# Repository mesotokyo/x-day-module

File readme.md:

# X-DAY (a.k.a. musicboxmod)

X-DAY (development name: musicboxmod) is a music box synthesizer module using HK326 IC. Based on the reference circuit, but modified to allow playback speed (and pitch) control. In addition, this module can output a gate signal linked to the melody.

## Controls, inputs and outputs

 - `START` button: Playback ON/OFF control. The behavior depoends on jumper pin settings
 - `SPEED` knob: Control playback speed. Also pitch changes with playback speed
 - `MOD CV IN`: Modulation input to change the playback speed
 - `TRIG IN`: Trigger input to control Playback ON/OFF (the same as `START` button)
 - `AUDIO OUT`: Audio signal output
 - `GATE OUT`: Gate signal output
 - `CV OFFSET`(trimmer resistor on PCB): You can change CV input offset. Recommended position is almost "2 o'clock" 
 - `MODE` (jumper pin on PCB): You can change the  behavior of the `START` button and the `TRIG IN` input. See table 1.
 - `SL` (jumper pin on PCB): You can change the  behavior of the `START` button and the `TRIG IN` input. See table 1.

### Table 1: `MODE` and `SL` jumper pin settings

| MODE pin setting | SL pin setting | Behavior |
| ---------------- | -------------- | -------- |
| Vdd              | Vdd            | ON/OFF   |
| Vdd              | Vss            | ONE SHOT, NON RE-TRIGGER |
| Vss              | Vdd            | ONE SHOT, RE-TRIGGER |
| Vss              | Vss            | PLAY ALL SONGS |

 - note 1: `Vss` is opposite position of `Vdd`.
 - note 2: `ONE SHOT` means "play one song and then stop".
 - note 3: `RE-TRIGGER` means "stop current song and play next song when the button is pushed".

## Schematic

## PCB image

## KiCAD files

This KiCAD project uses my KiCAD footprint and symbol library (https://github.com/mesotokyo/mst-kicad-lib). If you want to modify the schematic and PCB, please import this library.

## gerber

Please check [gerber](gerber) directory.

# Licenses

Creative Commons CC-BY 4.0 (https://creativecommons.org/licenses/by/4.0/)

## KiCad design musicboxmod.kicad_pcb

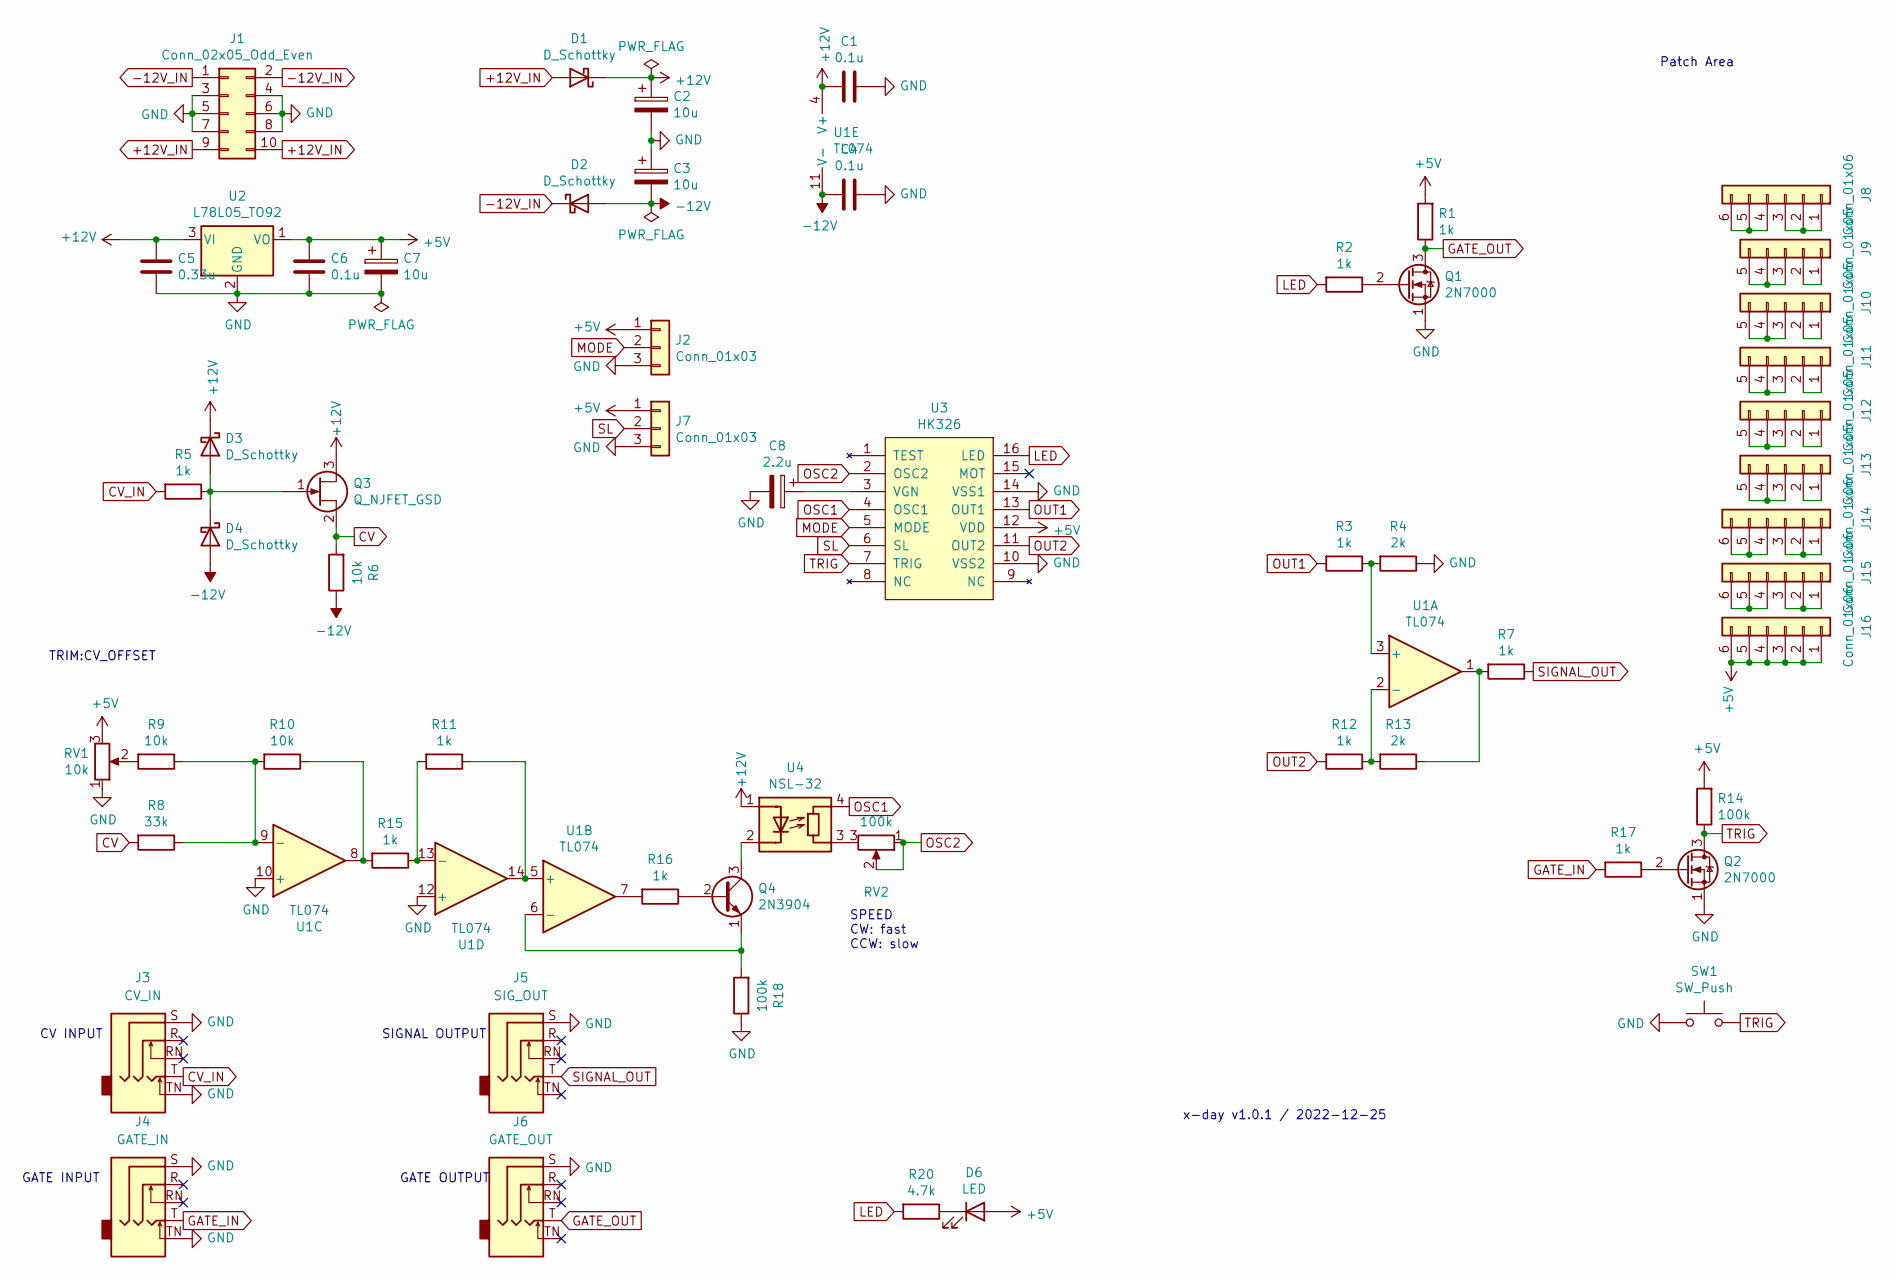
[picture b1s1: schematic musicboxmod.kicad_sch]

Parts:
C1, C4, C6: 0.1u; C_Disc_D3.0mm_W1.6mm_P2.50mm
C2, C3, C7: 10u; CP_Radial_D5.0mm_P2.50mm
C5: 0.33u; C_Disc_D3.0mm_W1.6mm_P2.50mm
C8: 2.2u; C_Disc_D3.0mm_W1.6mm_P2.50mm
D1, D2, D3, D4: D_Schottky; D_DO-34_SOD68_P7.62mm_Horizontal
D6: LED; LED_D3.0mm
J1: Conn_02x05_Odd_Even; IDC-Header_2x05_P2.54mm_Vertical
J2, J7: Conn_01x03; PinSocket_1x03_P2.54mm_Vertical
J3: CV_IN; Jack_3.5mm_CUI_SJ1-3535NG_Horizontal
J4: GATE_IN; Jack_3.5mm_CUI_SJ1-3535NG_Horizontal
J5: SIG_OUT; Jack_3.5mm_CUI_SJ1-3535NG_Horizontal
J6: GATE_OUT; Jack_3.5mm_CUI_SJ1-3535NG_Horizontal
J8, J14, J15, J16: Conn_01x06; PinHeader_1x06_P2.54mm_Vertical
J9, J10, J11, J12, J13: Conn_01x05; PinHeader_1x05_P2.54mm_Vertical
Q1, Q2: 2N7000; TO-92
Q3: Q_NJFET_GSD; TO-92
Q4: 2N3904; TO-92
R1, R2, R3, R5, R7, R11, R12, R15, R16, R17: 1k; R_Axial_DIN0204_L3.6mm_D1.6mm_P7.62mm_Horizontal
R4, R13: 2k; R_Axial_DIN0204_L3.6mm_D1.6mm_P7.62mm_Horizontal
R6, R9, R10: 10k; R_Axial_DIN0204_L3.6mm_D1.6mm_P7.62mm_Horizontal
R8: 33k; R_Axial_DIN0204_L3.6mm_D1.6mm_P7.62mm_Horizontal
R14, R18: 100k; R_Axial_DIN0204_L3.6mm_D1.6mm_P7.62mm_Horizontal
R20: 4.7k; R_Axial_DIN0204_L3.6mm_D1.6mm_P7.62mm_Horizontal
RV1: 10k; Potentiometer_Bourns_3339S_Horizontal
RV2: 100k; Potentiometer_Alps_RK097_Single_Horizontal
SW1: SW_Push; PinHeader_1x02_P2.54mm_Vertical
U1: TL074; DIP-14_W7.62mm_Socket
U2: L78L05_TO92; TO-92
U3: HK326; DIP-16_W7.62mm_Socket
U4: NSL-32; Luna_NSL-32

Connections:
+5V: C6.2, C7.1, D6.2 (A), J2.1, J7.1, J16.1, J16.2, J16.3, J16.4, J16.5, J16.6, R1.2, R14.2, RV1.3, U2.1 (VO), U3.12 (VDD)
+12V: C1.1, C2.1, C5.2, D1.1 (K), D3.1 (K), Q3.3 (D), U1.4 (V+), U2.3 (VI), U4.1 (A)
+12V_IN: D1.2 (A), J1.9, J1.10
-12V: C3.2, C4.1, D2.2 (A), D4.2 (A), R6.1, U1.11 (V-)
-12V_IN: D2.1 (K), J1.1, J1.2
CV: Q3.2 (S), R6.2, R8.2
CV_IN: J3.T, R5.2
GATE_IN: J4.T, R17.2
GATE_OUT: J6.T, Q1.3 (D), R1.1
GND: C1.2, C2.2, C3.1, C4.2, C5.1, C6.1, C7.2, C8.2, J1.3, J1.4, J1.5, J1.6, J1.7, J1.8, J2.3, J3.S, J3.TN, J4.S, J4.TN, J5.S, J6.S, J7.3, Q1.1 (S), Q2.1 (S), R4.1, R18.1, RV1.1, SW1.1, U1.10 (+), U1.12 (+), U2.2 (GND), U3.10 (VSS2), U3.14 (VSS1)
LED: R2.2, R20.2, U3.16 (LED)
MODE: J2.2, U3.5 (MODE)
unnamed: C8.1, U3.3 (VGN)
unnamed: D3.2 (A), D4.1 (K), Q3.1 (G), R5.1
unnamed: D6.1 (K), R20.1
unnamed: J8.1, J8.2, J8.3
unnamed: J8.4, J8.5, J8.6
unnamed: J9.1, J9.2
unnamed: J9.3, J9.4, J9.5
unnamed: J10.1, J10.2
unnamed: J10.3, J10.4, J10.5
unnamed: J11.1, J11.2
unnamed: J11.3, J11.4, J11.5
unnamed: J12.1, J12.2
unnamed: J12.3, J12.4, J12.5
unnamed: J13.1, J13.2
unnamed: J13.3, J13.4, J13.5
unnamed: J14.1, J14.2, J14.3
unnamed: J14.4, J14.5, J14.6
unnamed: J15.1, J15.2, J15.3
unnamed: J15.4, J15.5, J15.6
unnamed: Q1.2 (G), R2.1
unnamed: Q2.2 (G), R17.1
unnamed: Q4.1 (E), R18.2, U1.6 (-)
unnamed: Q4.2 (B), R16.1
unnamed: Q4.3 (C), U4.2 (K)
unnamed: R3.1, R4.2, U1.3 (+)
unnamed: R9.2, RV1.2
unnamed: R10.1, R15.2, U1.8
unnamed: R8.1, R9.1, R10.2, U1.9 (-)
unnamed: R11.1, U1.5 (+), U1.14
unnamed: R11.2, R15.1, U1.13 (-)
unnamed: R12.1, R13.2, U1.2 (-)
unnamed: R7.2, R13.1, U1.1
unnamed: R16.2, U1.7
unnamed: RV2.3, U4.3 (R)
OSC1: U3.4 (OSC1), U4.4 (R)
OSC2: RV2.1, RV2.2, U3.2 (OSC2)
OUT1: R3.2, U3.13 (OUT1)
OUT2: R12.2, U3.11 (OUT2)
SIGNAL_OUT: J5.T, R7.1
SL: J7.2, U3.6 (SL)
TRIG: Q2.3 (D), R14.1, SW1.2, U3.7 (TRIG)

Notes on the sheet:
CV INPUT
SIGNAL OUTPUT
TRIM:CV_OFFSET
GATE INPUT
x-day v1.0.1 / 2022-12-25
Patch Area
GATE OUTPUT
SPEED CW: fast CCW: slow

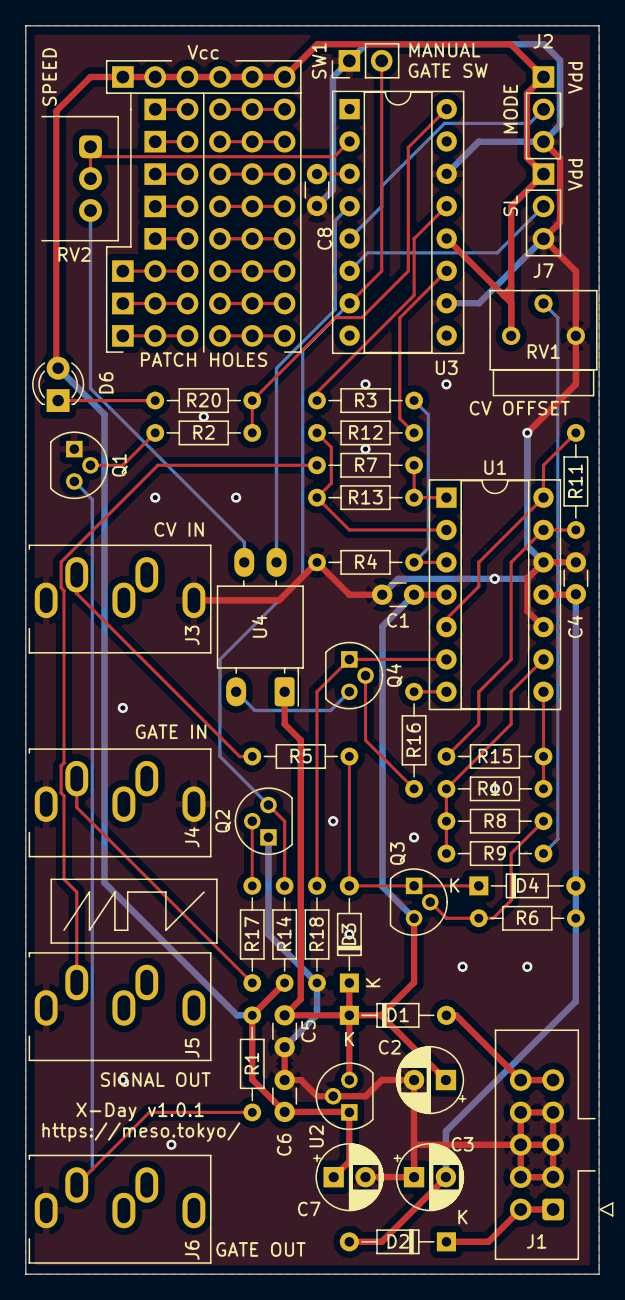
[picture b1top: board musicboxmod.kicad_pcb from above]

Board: 2 copper layers, 45.0 x 98.0 mm, 59 parts (0 on the bottom side), 53 nets.

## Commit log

2022-12-25 initial release
